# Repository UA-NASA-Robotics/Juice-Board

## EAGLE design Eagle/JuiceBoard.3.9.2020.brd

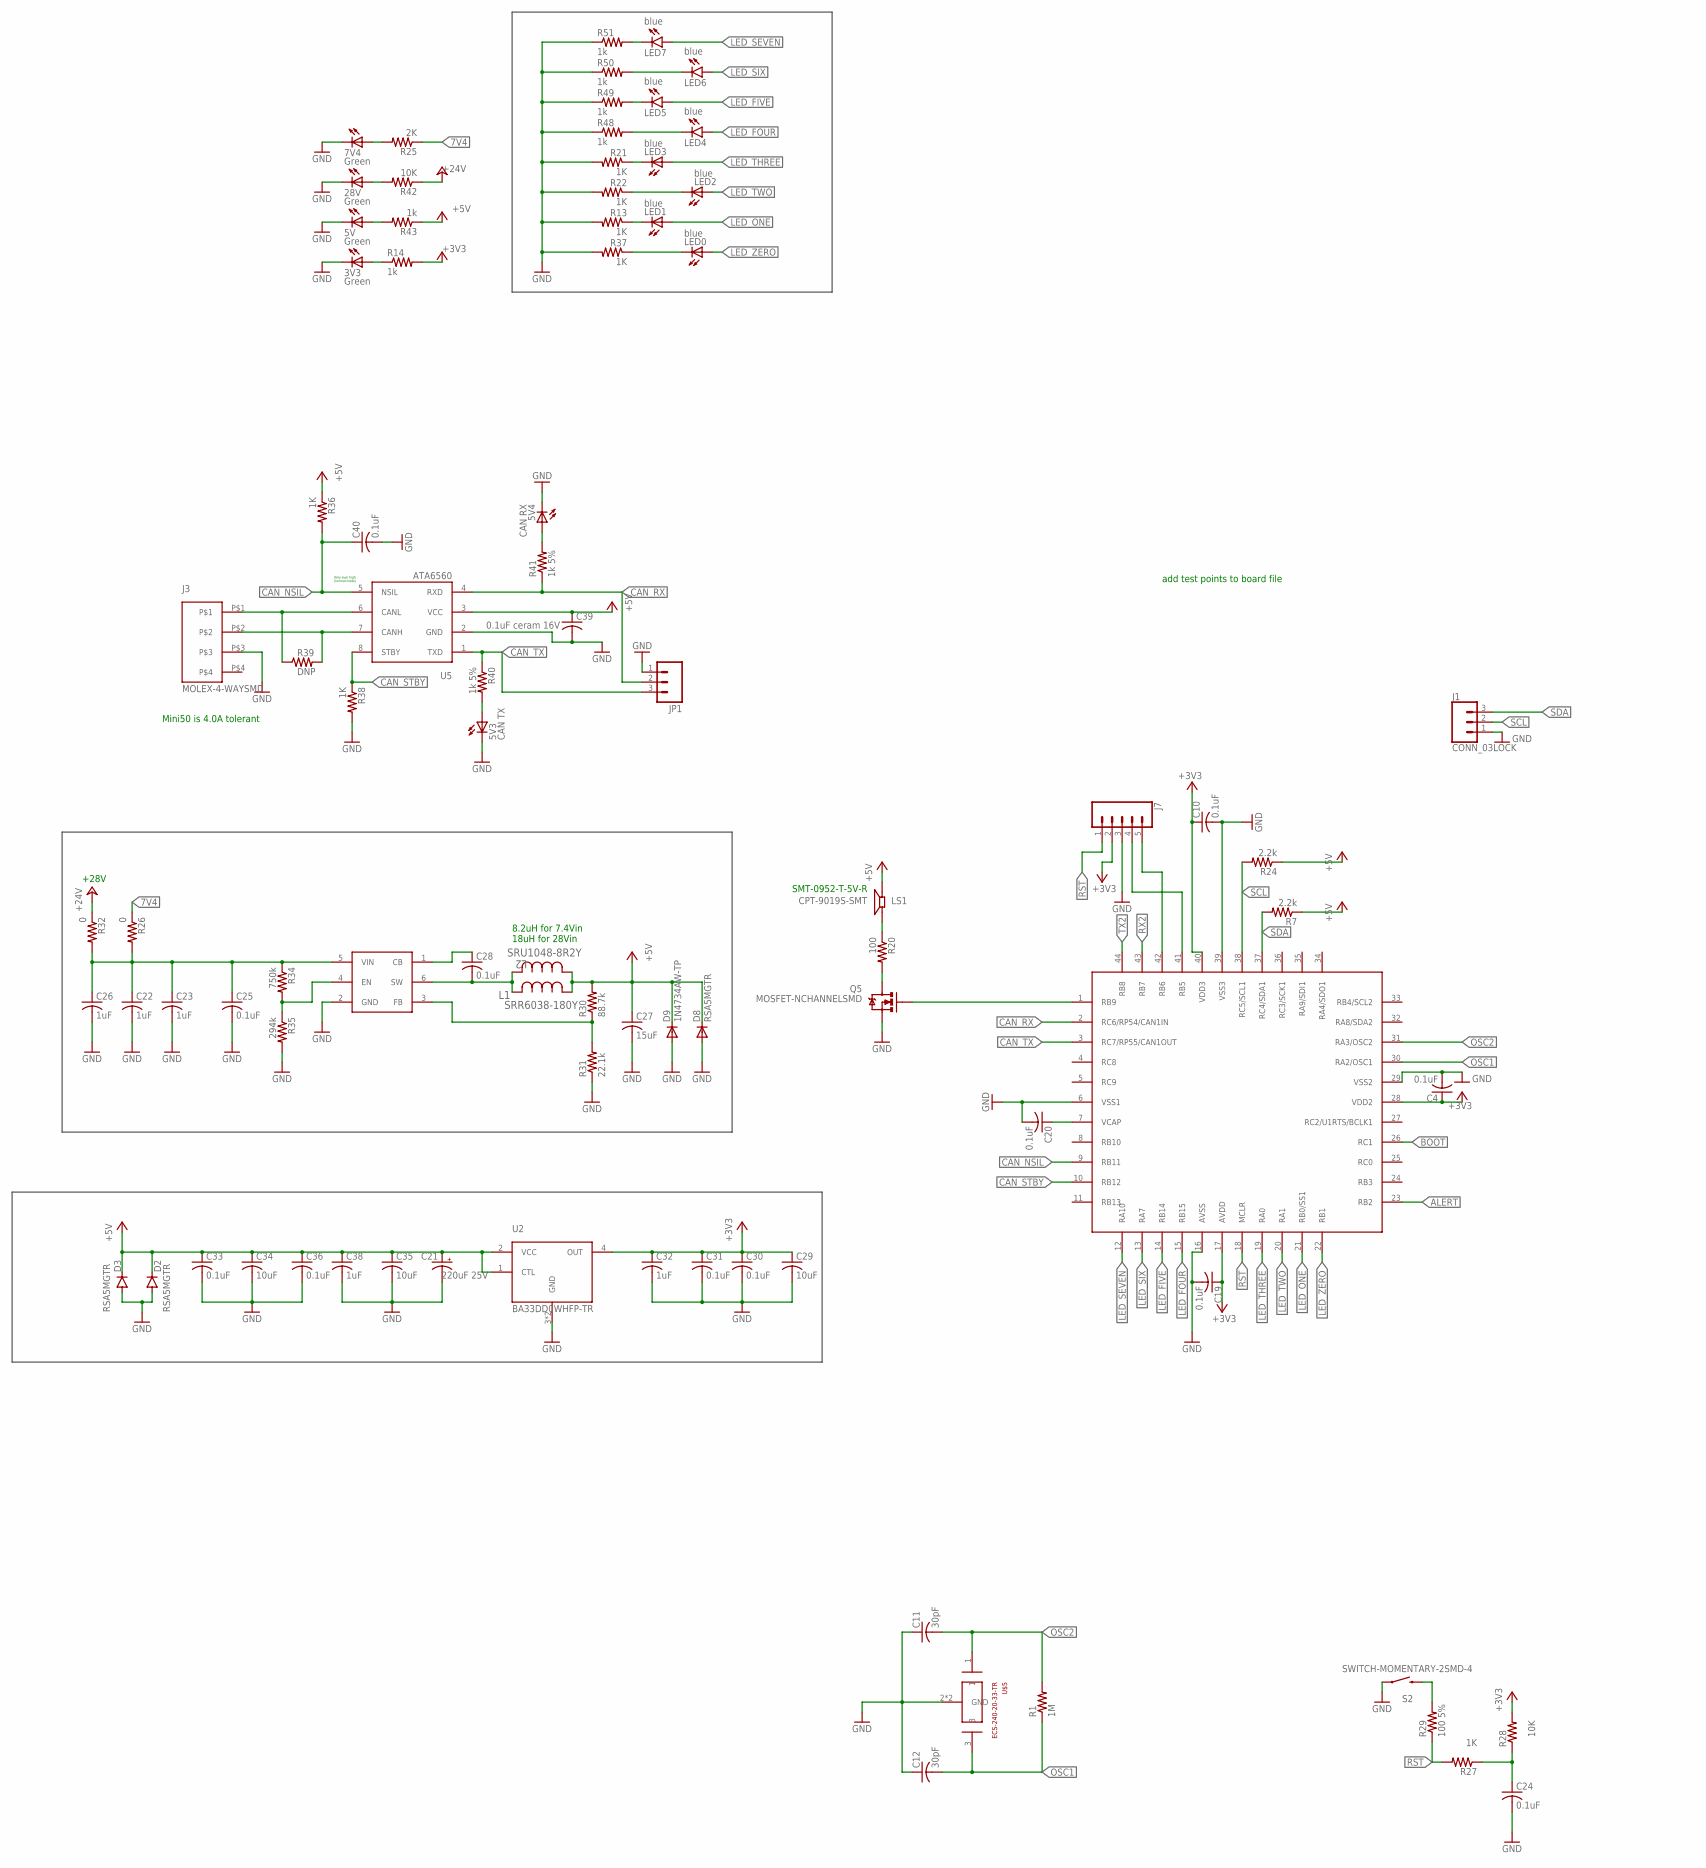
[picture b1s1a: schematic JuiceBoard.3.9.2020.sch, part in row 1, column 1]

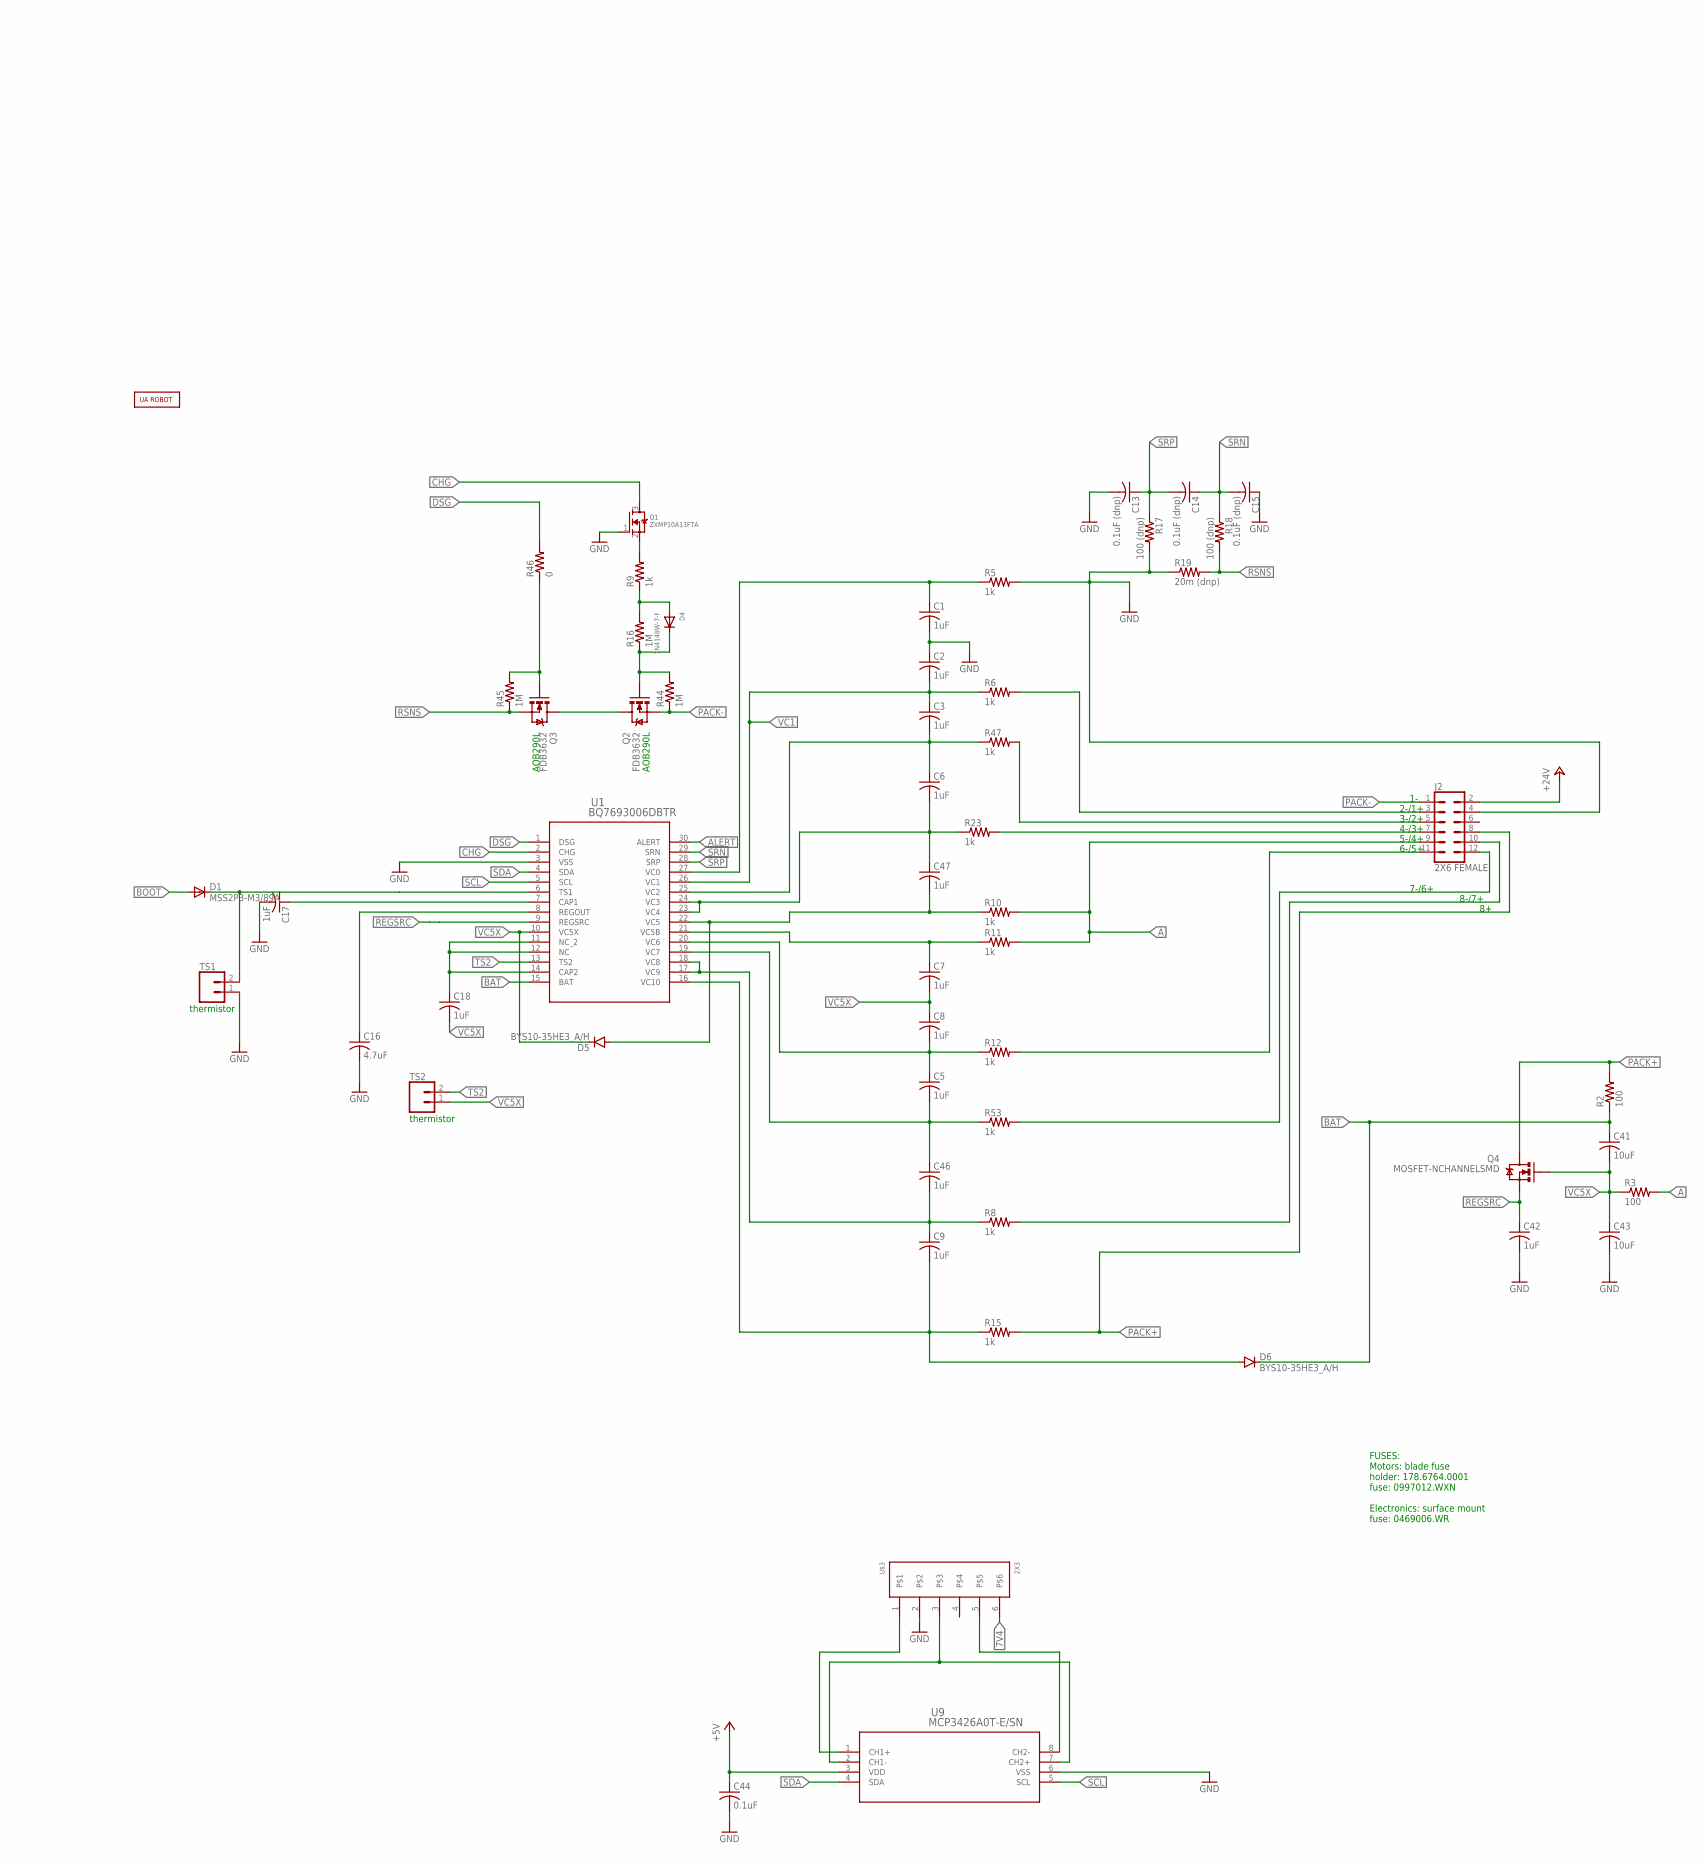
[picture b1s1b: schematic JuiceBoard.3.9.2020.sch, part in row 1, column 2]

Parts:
3V3: Green; CHIPLED_0805
5V, 7V4, 28V: Green; CHIP-LED0805
5V3: CAN TX; CHIP-LED0805
5V4: CAN RX; CHIP-LED0805
A1: NASA_LOGO; ROOBOT1
C1, C2, C3, C5, C6, C7, C8, C9, C17, C18, C22, C23, C26, C32, C38, C42, C46, C47: 1uF; C0805
C4, C10, C19, C20, C24, C25, C28, C30, C31, C33, C36, C40, C44: 0.1uF; C0805
C11, C12: 30pF; C0805
C13, C14, C15: 0.1uF (dnp); C0805
C16: 4.7uF; C0805
C21: 220uF 25V; 140CLH-1014
C27: 15uF; C0805
C29, C34, C35, C41, C43: 10uF; C0805
C39: 0.1uF ceram 16V; C0805
D1: MSS2P3-M3/89A; SOD123
D2, D3: RSA5MGTR; SOD-123_MINI-SMA
D4: 1N4148W-7-F; SOD-123
D5, D6: BYS10-35HE3_A/H; DO214AC
D8: RSA5MGTR; SOD123
D9: 1N4734AW-TP; SOD123
J1: CONN_03LOCK; 1X03_LOCK
J2: 2X6 FEMALE; 2X6
J3: MOLEX-4-WAYSMD; 4-WAY-SMD-90D
J7: CONN_05; 1X05
JP1: M03LOCK; 1X03_LOCK
L1: SRR6038-180Y; IND_BOURNS_SRR6038
L2: SRU1048-8R2Y; IND_BOURNS_SRU1048
LED0, LED1, LED2, LED3: blue; CHIPLED_0805
LED4, LED5, LED6, LED7: blue; CHIP-LED0805
LS1: CPT-9019S-SMT; CUI_CPT-9019S-SMT
Q1: ZXMP10A13FTA; SOT23
Q2, Q3: FDB3632; TO-263-2
Q4, Q5: MOSFET-NCHANNELSMD; SOT23-3
R1, R16, R44, R45: 1M; R0805
R2, R3: 100; R0805
R5, R6, R8, R10, R11, R12, R14, R15, R23, R43, R47, R53: 1k; M0805
R7, R24: 2.2k; R0805
R9, R48, R49, R50, R51: 1k; R0805
R13, R21, R22, R27, R36, R37, R38: 1K; M0805
R17, R18: 100 (dnp); M0805
R19: 20m (dnp); M0805
R20: 100; M0805
R25: 2K; M0805
R26, R32: 0; M0805
R28, R42: 10K; M0805
R29: 100 5%; M0805
R30: 88.7k; M0805
R31: 22.1k; M0805
R34: 750k; M0805
R35: 294k; M0805
R39: DNP; M0805
R40, R41: 1k 5%; M0805
R46: 0; R0805
S2: SWITCH-MOMENTARY-2SMD-4; TACTILE_SWITCH_TALL
TS1, TS2: CONN_02; 1X02
U1: BQ7693006DBTR; DBT30
U2: BA33DD0WHFP-TR; HRP5
U3: DSPIC33EP512GM604; TQFP-44
U5: ATA6560; SOIC8
U7: TPS560430YDBVR; SOT23-6
U9: MCP3426A0T-E/SN; SOIC8-N_MC
U$3: 2X3
U$5: ECS-240-20-33-TR; ECX-32

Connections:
7V4: R25.1, R26.1, U$3.6
+3V3: C4.1, C10.1, C19.1, C29.1, C30.1, C31.1, C32.1, J7.2, R14.2, R28.2, U2.4 (OUT), U3.17 (AVDD), U3.28 (VDD2), U3.40 (VDD3)
+5V: C21.+, C27.1, C33.1, C34.1, C35.1, C36.1, C38.1, C39.1, C44.1, D2.C, D3.C, D8.C, D9.C, L1.1, L2.1, LS1.2, R7.1, R24.1, R30.2, R36.1, R43.1, U2.1 (CTL), U2.2 (VCC), U5.3 (VCC), U9.3 (VDD)
+24V: J2.2, R32.1, R42.1
A: J2.9, R3.2, R10.2, R11.2
ALERT: U1.30 (ALERT), U3.23 (RB2)
BAT: C41.1, D6.C, R2.1, U1.15 (BAT)
BOOT: D1.A, U3.26 (RC1)
CAN_NSIL: C40.1, R36.2, U3.9 (RB11), U5.5 (NSIL)
CAN_RX: JP1.2, R41.1, U3.2 (RC6/RP54/CAN1IN), U5.4 (RXD)
CAN_STBY: R38.1, U3.10 (RB12), U5.8 (STBY)
CAN_TX: JP1.3, R40.1, U3.3 (RC7/RP55/CAN1OUT), U5.1 (TXD)
CHG: Q1.3 (D), U1.2 (CHG)
DSG: R46.2, U1.1 (DSG)
GND: 3V3.C, 5V.C, 5V3.C, 5V4.C, 7V4.C, 28V.C, C1.2, C2.1, C4.2, C10.2, C11.1, C12.1, C13.2, C15.1, C16.2, C17.2, C19.2, C20.2, C21.-, C22.2, C23.2, C24.2, C25.2, C26.2, C27.2, C29.2, C30.2, C31.2, C32.2, C33.2, C34.2, C35.2, C36.2, C38.2, C39.2, C40.2, C42.2, C43.2, C44.2, D2.A, D3.A, D8.A, D9.A, J1.1, J2.4, J3.P$3, J7.3, JP1.1, Q1.1 (G), Q5.2 (S), R5.2, R13.2, R17.2, R19.1, R21.2, R22.2, R31.1, R35.2, R37.2, R38.2, R48.1, R49.1, R50.1, R51.1, S2.A2 (1), TS1.1, U1.3 (VSS), U2.3 (GND), U2.G (GND), U3.6 (VSS1), U3.16 (AVSS), U3.29 (VSS2), U3.39 (VSS3), U5.2 (GND), U7.2 (GND), U9.6 (VSS), U$3.2, U$5.2 (GND), U$5.4 (GND)
LED_FIVE: LED5.A, U3.14 (RB14)
LED_FOUR: LED4.A, U3.15 (RB15)
LED_ONE: LED1.A, U3.21 (RB0/SS1)
LED_SEVEN: LED7.A, U3.12 (RA10)
LED_SIX: LED6.A, U3.13 (RA7)
LED_THREE: LED3.A, U3.19 (RA0)
LED_TWO: LED2.A, U3.20 (RA1)
LED_ZERO: LED0.A, U3.22 (RB1)
unnamed: Q5.1 (G), U3.1 (RB9)
unnamed: Q5.3 (D), R20.2
unnamed: C16.1, U1.8 (REGOUT)
unnamed: C3.2, C6.1, R47.1, U1.25 (VC2)
unnamed: C7.1, R11.1, U1.21 (VC5B)
unnamed: C1.1, R5.1, U1.27 (VC0)
unnamed: J7.5, U3.42 (RB6)
unnamed: Q1.2 (S), R9.2
unnamed: J7.4, U3.41 (RB5)
unnamed: C5.1, C8.2, R12.1, U1.20 (VC6)
unnamed: D4.A, R9.1, R16.2
unnamed: J2.12, R53.2
unnamed: C9.1, C46.2, R8.1, U1.17 (VC9), U1.18 (VC8)
unnamed: LED7.C, R51.2
unnamed: D4.C, Q2.3 (G), R16.1, R44.2
unnamed: C9.2, D6.A, R15.1, U1.16 (VC10)
unnamed: LED6.C, R50.2
unnamed: J2.3, R6.2
unnamed: Q2.1 (D), Q3.1 (D)
unnamed: C47.2, D5.A, R10.1, U1.22 (VC5)
unnamed: C18.1, U1.11 (NC_2), U1.12 (NC), U1.14 (CAP2)
unnamed: J2.11, R12.2
unnamed: 7V4.A, R25.2
unnamed: J2.10, R8.2
unnamed: J2.5, R47.2
unnamed: D1.C, TS1.2, U1.6 (TS1)
unnamed: C22.1, C23.1, C25.1, C26.1, R26.2, R32.2, R34.1, U7.5 (VIN)
unnamed: C17.1, U1.7 (CAP1)
unnamed: C6.2, C47.1, R23.1, U1.23 (VC4), U1.24 (VC3)
unnamed: Q3.3 (G), R45.2, R46.1
unnamed: LS1.1, R20.1
unnamed: 3V3.A, R14.1
unnamed: LED5.C, R49.2
unnamed: J2.7, R23.2
unnamed: C20.1, U3.7 (VCAP)
unnamed: LED4.C, R48.2
unnamed: LED3.C, R21.1
unnamed: LED2.C, R22.1
unnamed: LED1.C, R13.1
unnamed: LED0.C, R37.1
unnamed: C24.1, R27.1, R28.1
unnamed: R29.2, S2.B2 (2)
unnamed: C28.2, L1.2, L2.2, U7.6 (SW)
unnamed: C28.1, U7.1 (CB)
unnamed: R30.1, R31.2, U7.3 (FB)
unnamed: R34.2, R35.1, U7.4 (EN)
unnamed: J3.P$2, R39.2, U5.7 (CANH)
unnamed: 5V3.A, R40.2
unnamed: 5V4.A, R41.2
unnamed: J3.P$1, R39.1, U5.6 (CANL)
unnamed: 28V.A, R42.2
unnamed: 5V.A, R43.2
unnamed: U9.1 (CH1+), U$3.1
unnamed: U9.2 (CH1-), U9.7 (CH2+), U$3.3
unnamed: U9.8 (CH2-), U$3.5
unnamed: C5.2, C46.1, R53.1, U1.19 (VC7)
OSC1: C12.2, R1.1, U3.30 (RA2/OSC1), U$5.3
OSC2: C11.2, R1.2, U3.31 (RA3/OSC2), U$5.1
PACK+: J2.8, Q4.3 (D), R2.2, R15.2
PACK-: J2.1, Q2.TAB (S), R44.1
REGSRC: C42.1, Q4.2 (S), U1.9 (REGSRC)
RSNS: Q3.TAB (S), R18.2, R19.2, R45.1
RST: J7.1, R27.2, R29.1, U3.18 (MCLR)
RX2: U3.43 (RB7)
SCL: J1.2, R24.2, U1.5 (SCL), U3.38 (RC5/SCL1), U9.5 (SCL)
SDA: J1.3, R7.2, U1.4 (SDA), U3.37 (RC4/SDA1), U9.4 (SDA)
SRN: C14.1, C15.2, R18.1, U1.29 (SRN)
SRP: C13.1, C14.2, R17.1, U1.28 (SRP)
TS2: TS2.2, U1.13 (TS2)
TX2: U3.44 (RB8)
VC1: C2.2, C3.1, R6.1, U1.26 (VC1)
VC5X: C7.2, C8.1, C18.2, C41.2, C43.1, D5.C, Q4.1 (G), R3.1, TS2.1, U1.10 (VC5X)

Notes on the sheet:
+28V
Only ever high (normal mode)
Mini50 is 4.0A tolerant
AOB290L
FUSES: Motors: blade fuse holder: 178.6764.0001 fuse: 0997012.WXN Electronics: surface mount fuse: 0469006.WR
add test points to board file
thermistor
8-/7+
7-/6+
6-/5+
5-/4+
4-/3+
3-/2+
2-/1+
8.2uH for 7.4Vin 18uH for 28Vin
SMT-0952-T-5V-R

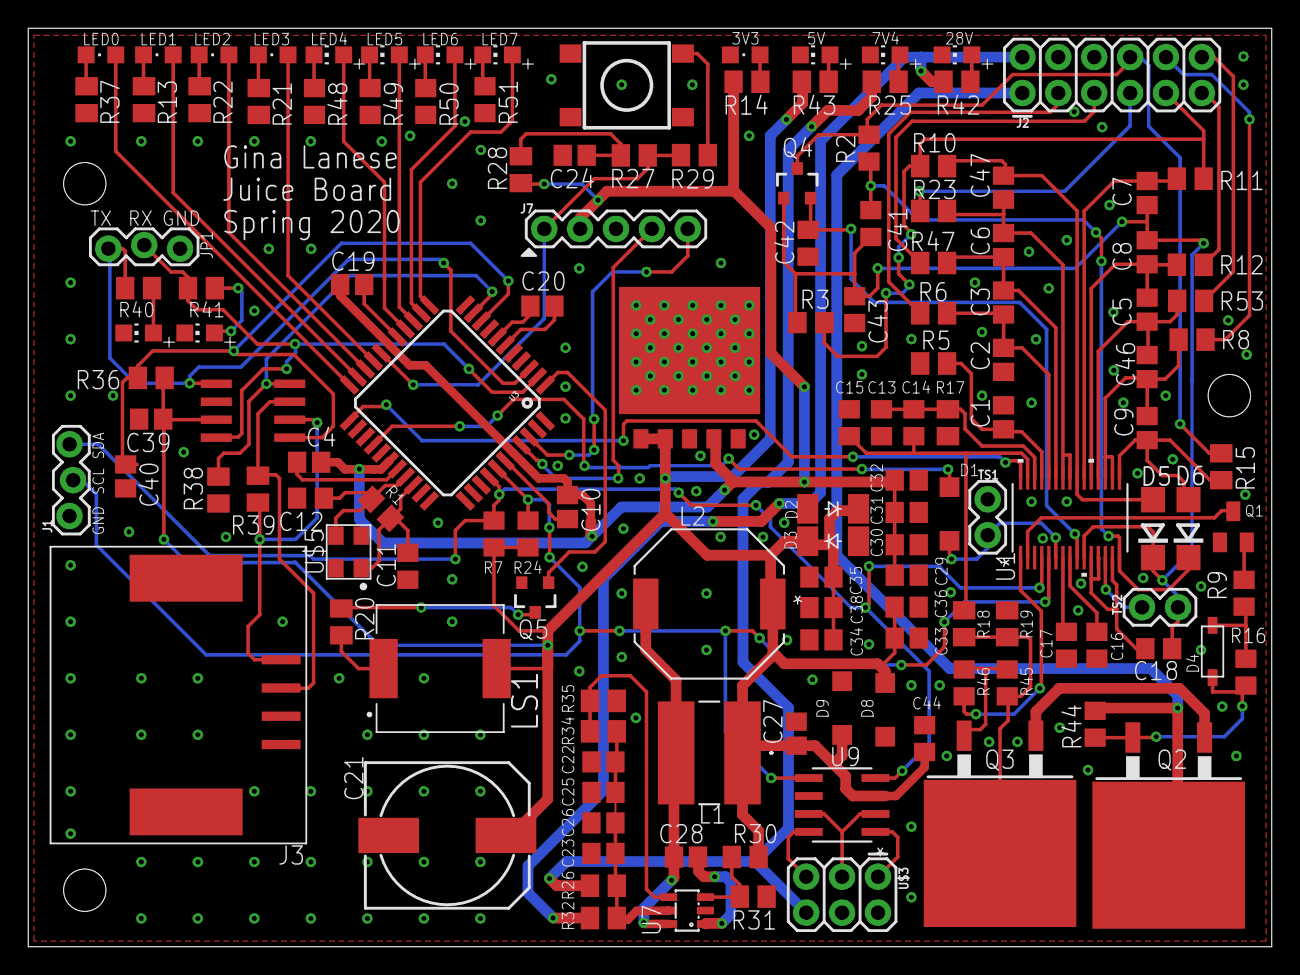
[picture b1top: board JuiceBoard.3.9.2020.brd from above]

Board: 2 copper layers, 88.0 x 65.0 mm, 142 parts (1 on the bottom side), 93 nets.

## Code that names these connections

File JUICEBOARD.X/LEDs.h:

/* 
 * File:   LEDs.h
 * Author: Jaret
 *
 * Created on September 4, 2020, 10:17 PM
 */

#ifndef LEDS_H
#define	LEDS_H

#define LED_ZERO LATBbits.LATB1
#define LED_ONE LATBbits.LATB0
#define LED_TWO LATAbits.LATA1
#define LED_THREE LATAbits.LATA0
#define LED_FOUR LATBbits.LATB15
#define LED_FIVE LATBbits.LATB14
#define LED_SIX LATAbits.LATA7
#define LED_SEVEN LATAbits.LATA10

void LEDsAllOn(void);
void LEDsAllOff(void);
void LEDsAllToggle(void);


void initializeLEDs(void);

#ifdef	__cplusplus
extern "C" {
#endif




#ifdef	__cplusplus
}
#endif

#endif	/* LEDS_H */

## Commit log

2020-04-18 Show how Github works
2020-09-03 Add datasheets for BQ7693006DBTR
2020-09-03 Add EAGLE board files for reference
2020-09-03 Initial commit to move files to MPLab X project
2020-09-04 Rearrange docs, add datasheets for PIC33EP512GM604
2020-09-04 Create code configuration based on router card mcc
2020-09-05 Add gitignore, simple program to test LEDs
2020-09-05 Remove gitignored files
2020-09-05 Fix LED shared analog pins not going high.
2020-09-05 Use LAT instead of PORT for setting digital outputs
2020-09-08 Add buzzer functionality
2020-09-09 Change timer2 to 16bit for simplicity, change PR to 0xBB2
    This gives the timer a period of 0.9999332 ms. Close enough.
2020-09-09 Update gitignore for mplab subdirectory
2020-09-09 Use primary oscillator and change clock ratios for nicer numbers
    This should give a timer period of 'exactly' 1ms
2020-09-24 Model timer functionality from Master-Controller
2020-09-24 Test buzzer using timers
2020-09-25 Add buzzer on duration and timers
2020-10-08 Lower processor clock speed
2020-10-09 Add structure for state machine
2020-10-29 Write i2c address for referencing

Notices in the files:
parts and their libraries:
SparkFun-Connectors: Licensing: Creative Commons ShareAlike 4.0 International - https://creativecommons.org/licenses/by-sa/4.0
